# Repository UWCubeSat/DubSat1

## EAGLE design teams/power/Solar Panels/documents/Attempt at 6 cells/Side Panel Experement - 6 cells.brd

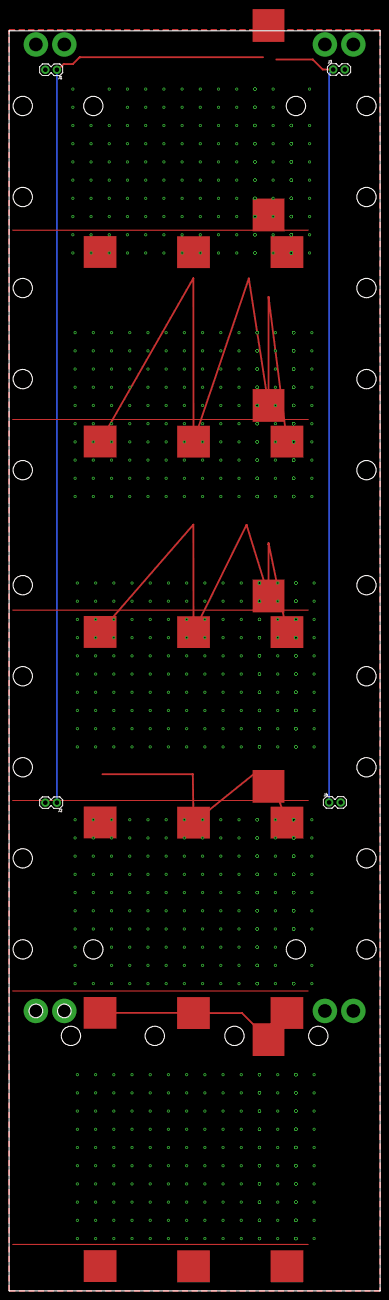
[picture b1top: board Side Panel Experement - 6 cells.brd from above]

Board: 2 copper layers, 81.5 x 276.8 mm, 10 parts (0 on the bottom side), 7 nets.

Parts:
J1, J2, J3, J4: 1X02
SOLAR_1, SOLAR_2, SOLAR_3, SOLAR_4, SOLAR_5, SOLAR_6: SOLAR_CELL_HALF_TABSFULL_TABS; SOLAR_CELL_3G30A_FULL_TABS

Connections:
1-2: SOLAR_1.P$1, SOLAR_2.P$F1, SOLAR_2.P$F2, SOLAR_2.P$F3
2-3: SOLAR_2.P$1, SOLAR_3.P$F1, SOLAR_3.P$F2, SOLAR_3.P$F3
3-4: SOLAR_3.P$1, SOLAR_4.P$F1, SOLAR_4.P$F2, SOLAR_4.P$F3
4-5: SOLAR_4.P$1, SOLAR_5.P$F1, SOLAR_5.P$F2, SOLAR_5.P$F3
GND: J1.2, J2.2, J3.2, J4.2, SOLAR_1.P$F1, SOLAR_1.P$F2, SOLAR_1.P$F3
unnamed: SOLAR_5.P$1, SOLAR_6.P$F1, SOLAR_6.P$F2, SOLAR_6.P$F3
VOUT: J1.1, J2.1, J3.1, J4.1

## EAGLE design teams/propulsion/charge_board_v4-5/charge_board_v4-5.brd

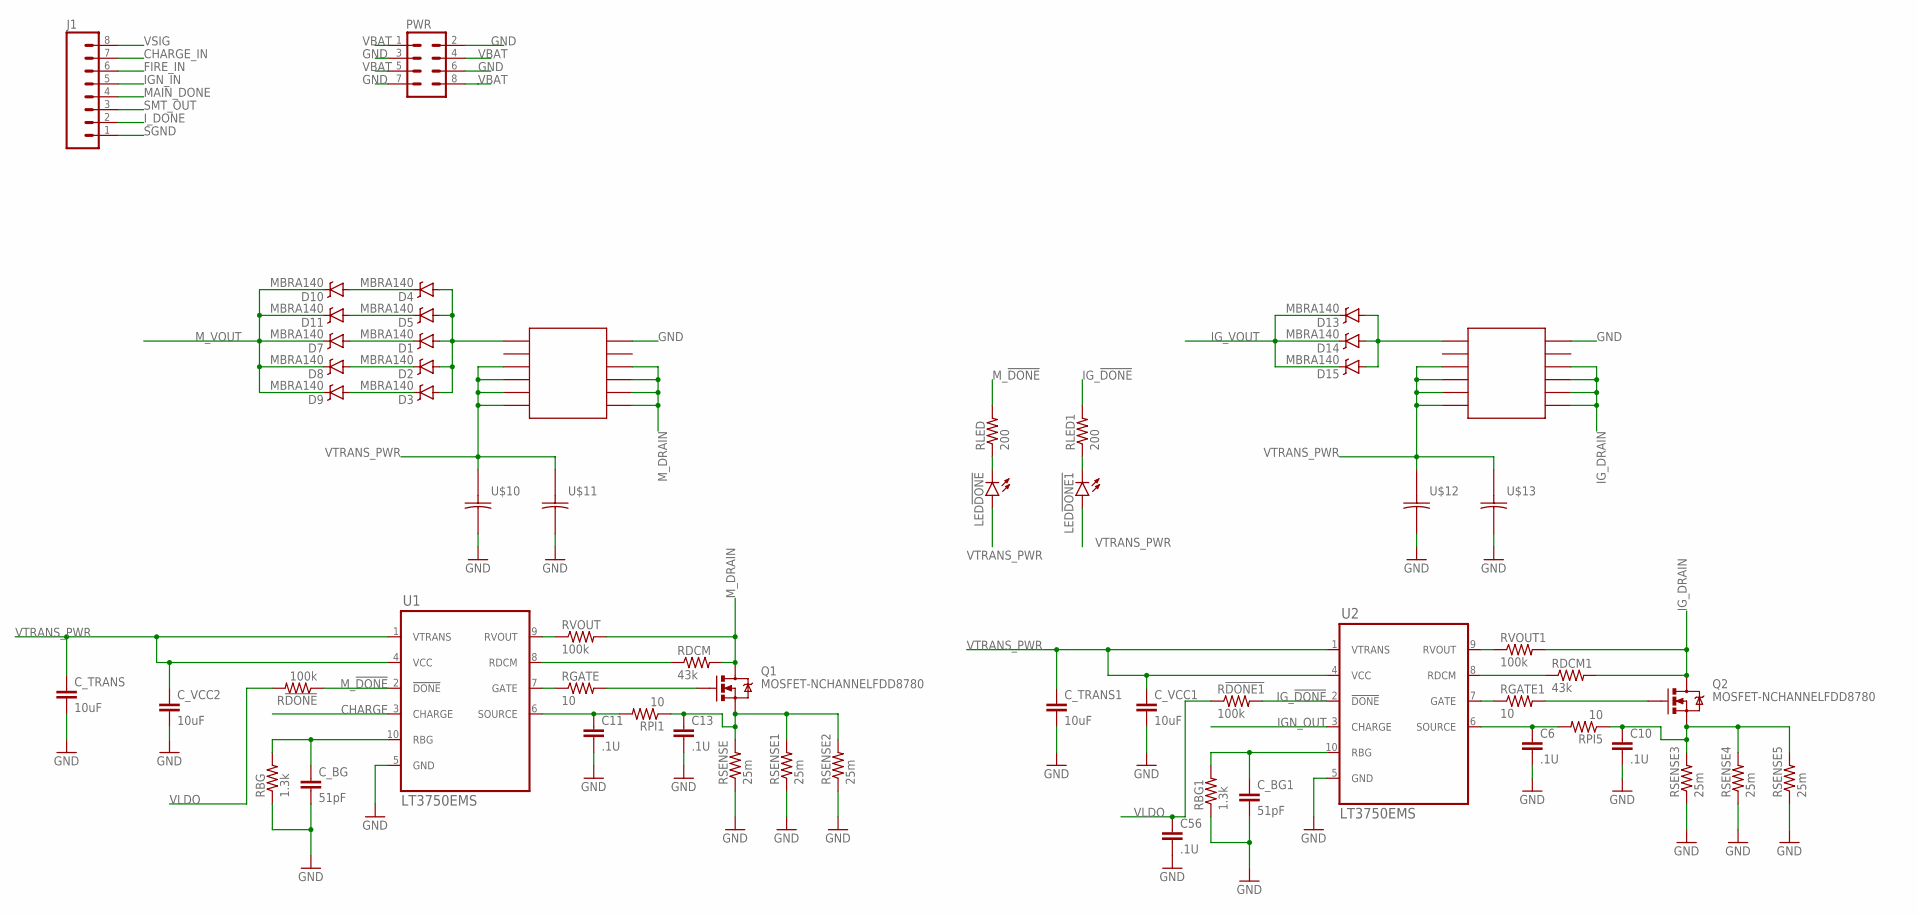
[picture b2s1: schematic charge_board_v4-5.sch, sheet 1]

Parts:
C6, C10, C11, C13, C56: .1U; 0805
C_BG, C_BG1: 51pF; 0805
C_TRANS, C_TRANS1: 10uF; 0805
C_VCC1, C_VCC2: 10uF; 0805
D1, D2, D3, D4, D5, D7, D8, D9, D10, D11, D13, D14, D15: MBRA140; SMA-DIODE
J1: M08; 1X08_ROUND
LED!DONE, LED!DONE1: LED1206; LED-1206
PWR: M04X2; 2X4
Q1, Q2: MOSFET-NCHANNELFDD8780; DPAK
R!DONE, R!DONE1: 100k; 0805
RBG, RBG1: 1.3k; 0805
RDCM, RDCM1: 43k; 0805
RGATE, RGATE1: 10; 0805
RLED, RLED1: 200; 0805
RPI1, RPI5: 10; 0805
RSENSE, RSENSE1, RSENSE2, RSENSE3, RSENSE4, RSENSE5: 25m; 0805
RVOUT, RVOUT1: 100k; 0805
U1, U2: LT3750EMS; MSOP10
U$1: COILCRAFT_DA2034; DA2034
U$2: COILCRAFT_DA2033; DA2033
U$10, U$11, U$12, U$13: PANASONIC_16SVPG270M; PANASONIC_SVPG

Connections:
7: RGATE1.1, U2.7 (GATE)
8: RDCM1.1, U2.8 (RDCM)
9: RVOUT1.1, U2.9 (RVOUT)
CHARGE: U1.3 (CHARGE); also elsewhere on the board
CHARGE_IN: J1.7; also elsewhere on the board
FIRE_IN: J1.6; also elsewhere on the board
GND: C6.2, C10.2, C11.2, C13.2, C56.2, C_BG.2, C_BG1.2, C_TRANS.2, C_TRANS1.2, C_VCC1.2, C_VCC2.2, PWR.2, PWR.3, PWR.6, PWR.7, RBG.1, RBG1.1, RSENSE.1, RSENSE1.1, RSENSE2.1, RSENSE3.1, RSENSE4.1, RSENSE5.1, U1.5 (GND), U2.5 (GND), U$1.P$12, U$2.P$12, U$10.NEG, U$11.NEG, U$12.NEG, U$13.NEG; also elsewhere on the board
IGN_IN: J1.5; also elsewhere on the board
IGN_OUT: U2.3 (CHARGE); also elsewhere on the board
IG_!DONE: R!DONE1.2, RLED1.2, U2.2 (!DONE); also elsewhere on the board
IG_BG: C_BG1.1, RBG1.2, U2.10 (RBG)
IG_DRAIN: Q2.4 (D), RDCM1.2, RVOUT1.2, U$2.P$7, U$2.P$8, U$2.P$9, U$2.P$10
IG_GATE: Q2.1 (G), RGATE1.2
IG_SENSE: C10.1, Q2.3 (S), RPI5.1, RSENSE3.2, RSENSE4.2, RSENSE5.2
IG_VOUT: D13.C, D14.C, D15.C; also elsewhere on the board
I_DONE: J1.2; also elsewhere on the board
MAIN_DONE: J1.4; also elsewhere on the board
M_!DONE: R!DONE.1, RLED.2, U1.2 (!DONE); also elsewhere on the board
M_BG: C_BG.1, RBG.2, U1.10 (RBG)
M_DRAIN: Q1.4 (D), RDCM.2, RVOUT.2, U$1.P$7, U$1.P$8, U$1.P$9, U$1.P$10
M_GATE: Q1.1 (G), RGATE.2
M_SCHMITT: J1.2
M_SENSE: C13.1, Q1.3 (S), RPI1.1, RSENSE.2, RSENSE1.2, RSENSE2.2
M_VOUT: D7.C, D8.C, D9.C, D10.C, D11.C; also elsewhere on the board
unnamed: C6.1, RPI5.2, U2.6 (SOURCE)
unnamed: RVOUT.1, U1.9 (RVOUT)
unnamed: D4.C, D10.A
unnamed: RDCM.1, U1.8 (RDCM)
unnamed: RGATE.1, U1.7 (GATE)
unnamed: D5.C, D11.A
unnamed: D1.C, D7.A
unnamed: D2.C, D8.A
unnamed: D3.C, D9.A
unnamed: LED!DONE.C, RLED.1
unnamed: LED!DONE1.C, RLED1.1
unnamed: D1.A, D2.A, D3.A, D4.A, D5.A, U$1.P$1
unnamed: C11.1, RPI1.2, U1.6 (SOURCE)
unnamed: D13.A, D14.A, D15.A, U$2.P$1
SGND: J1.1; also elsewhere on the board
SMT_OUT: J1.3; also elsewhere on the board
VBAT: PWR.1, PWR.4, PWR.5, PWR.8; also elsewhere on the board
VLDO: C56.1, R!DONE.2, R!DONE1.1; also elsewhere on the board
VSIG: J1.8; also elsewhere on the board
VTRANS_PWR: C_TRANS.1, C_TRANS1.1, C_VCC1.1, C_VCC2.1, LED!DONE.A, LED!DONE1.A, U1.1 (VTRANS), U1.4 (VCC), U2.1 (VTRANS), U2.4 (VCC), U$1.P$3, U$1.P$4, U$1.P$5, U$1.P$6, U$2.P$3, U$2.P$4, U$2.P$5, U$2.P$6, U$10.POS, U$11.POS, U$12.POS, U$13.POS; also elsewhere on the board

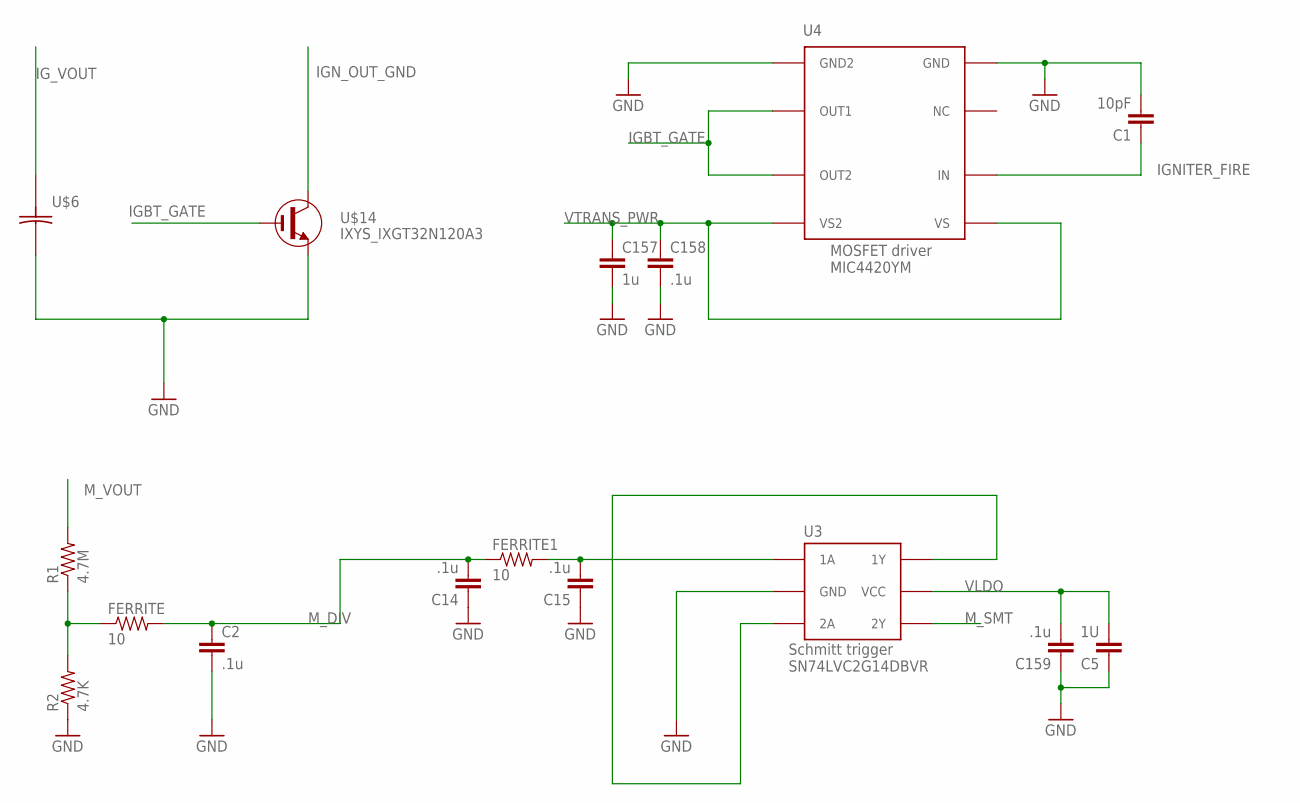
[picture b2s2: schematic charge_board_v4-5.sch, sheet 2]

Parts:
C1: 10pF; 0805
C2, C14, C15, C158, C159: .1u; 0805
C5: 1U; 0805
C157: 1u; 0805
FERRITE, FERRITE1: 10; 0805
R1: 4.7M; R2010
R2: 4.7K; R2010
U3: TI_SCHMITTRIGGER_SN74; SOT-23-6
U4: MICREL_MOSFETDRIVER_MIC4420; 8-SOIC
U$6: KEMET_LDEQH3100KA5N00; KEMET_F3078
U$14: IXYS_IXGT32N120A3; TO-268

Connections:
GND: C1.2, C2.2, C5.1, C14.1, C15.1, C157.2, C158.2, C159.1, R2.1, U3.P$2 (GND), U4.P$4 (GND), U4.P$5 (GND2), U$6.NEG, U$14.3 (E); also elsewhere on the board
IGBT_GATE: U4.P$6 (OUT1), U4.P$7 (OUT2), U$14.1 (G)
IGNITER_FIRE: C1.1, U4.P$2 (IN); also elsewhere on the board
IGN_OUT_GND: U$14.2 (C)
IG_VOUT: U$6.POS; also elsewhere on the board
M_DIV: C2.1, C14.2, FERRITE.2, FERRITE1.1
M_SMT: U3.P$4 (2Y); also elsewhere on the board
M_VOUT: R1.2; also elsewhere on the board
unnamed: U3.P$3 (2A), U3.P$6 (1Y)
unnamed: C15.2, FERRITE1.2, U3.P$1 (1A)
unnamed: FERRITE.1, R1.1, R2.2
VLDO: C5.2, C159.2, U3.P$5 (VCC); also elsewhere on the board
VTRANS_PWR: C157.1, C158.1, U4.P$1 (VS), U4.P$8 (VS2); also elsewhere on the board

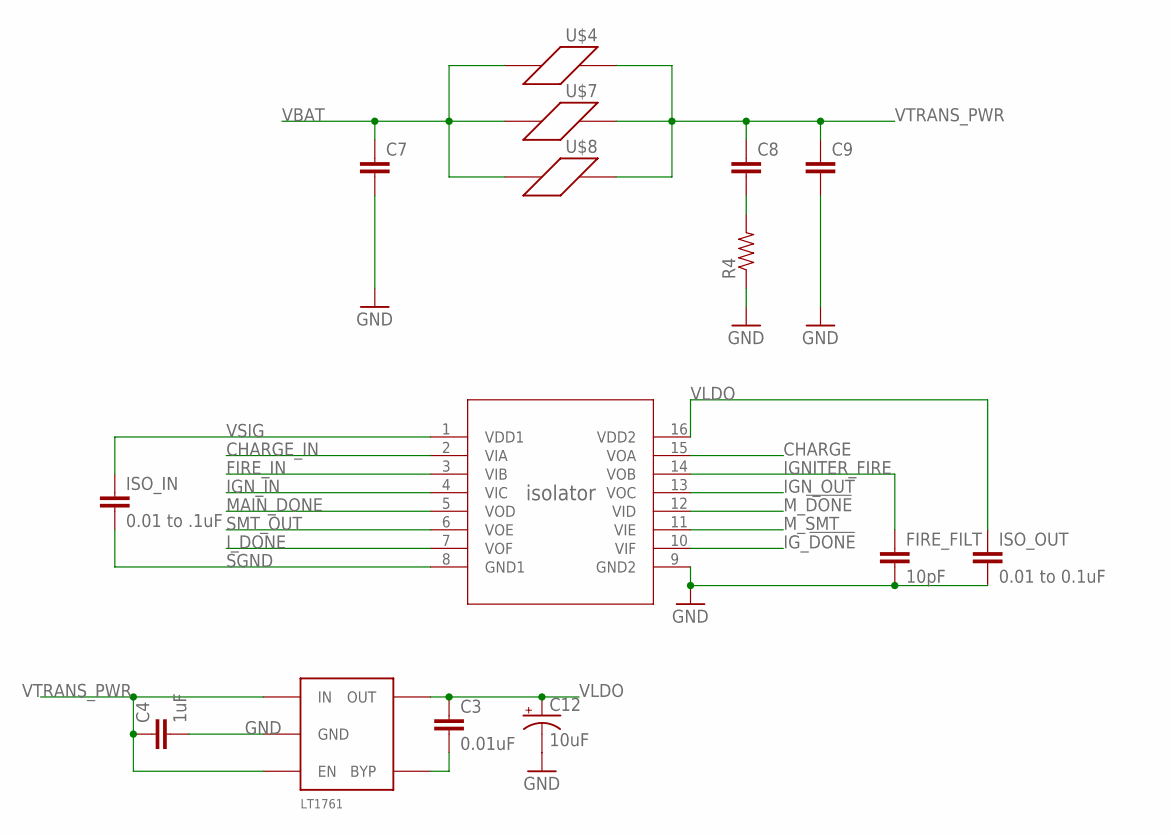
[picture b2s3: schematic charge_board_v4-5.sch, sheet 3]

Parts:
ADUM163N: ADUM163N1BRZ; R_16
C3: 0.01uF; 0805
C4: 1uF; 0805
C7, C8, C9: CAP0805; 0805
C12: 10uF; EIA3216
FIRE_FILT: 10pF; 0805
ISO_IN: 0.01 to .1uF; 0805
ISO_OUT: 0.01 to 0.1uF; 0805
LDO: LINEAR_LDO_LT1761-X; SOT-23-5
R4: RESISTOR0805-RES; 0805
U$4: B.L1_FBMJ2125HS420-T; 0805
U$7: B.L2_FBMH1608HL121-T; 0603
U$8: I.L1_587-3855-1-ND; 1206

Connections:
CHARGE: ADUM163N.15 (VOA); also elsewhere on the board
CHARGE_IN: ADUM163N.2 (VIA); also elsewhere on the board
FIRE_IN: ADUM163N.3 (VIB); also elsewhere on the board
GND: ADUM163N.9 (GND2), C4.2, C7.2, C9.2, C12.C (-), FIRE_FILT.2, ISO_OUT.2, LDO.P$2 (GND), R4.1; also elsewhere on the board
IGNITER_FIRE: ADUM163N.14 (VOB), FIRE_FILT.1; also elsewhere on the board
IGN_IN: ADUM163N.4 (VIC); also elsewhere on the board
IGN_OUT: ADUM163N.13 (VOC); also elsewhere on the board
IG_!DONE: ADUM163N.10 (VIF); also elsewhere on the board
I_DONE: ADUM163N.7 (VOF); also elsewhere on the board
MAIN_DONE: ADUM163N.5 (VOD); also elsewhere on the board
M_!DONE: ADUM163N.12 (VID); also elsewhere on the board
M_SMT: ADUM163N.11 (VIE); also elsewhere on the board
unnamed: C3.2, LDO.P$4 (BYP)
unnamed: C8.2, R4.2
SGND: ADUM163N.8 (GND1), ISO_IN.2; also elsewhere on the board
SMT_OUT: ADUM163N.6 (VOE); also elsewhere on the board
VBAT: C7.1, U$4.1, U$7.1, U$8.1; also elsewhere on the board
VLDO: ADUM163N.16 (VDD2), C3.1, C12.A (+), ISO_OUT.1, LDO.P$5 (OUT); also elsewhere on the board
VSIG: ADUM163N.1 (VDD1), ISO_IN.1; also elsewhere on the board
VTRANS_PWR: C4.1, C8.1, C9.1, LDO.P$1 (IN), LDO.P$3 (EN), U$4.2, U$7.2, U$8.2; also elsewhere on the board

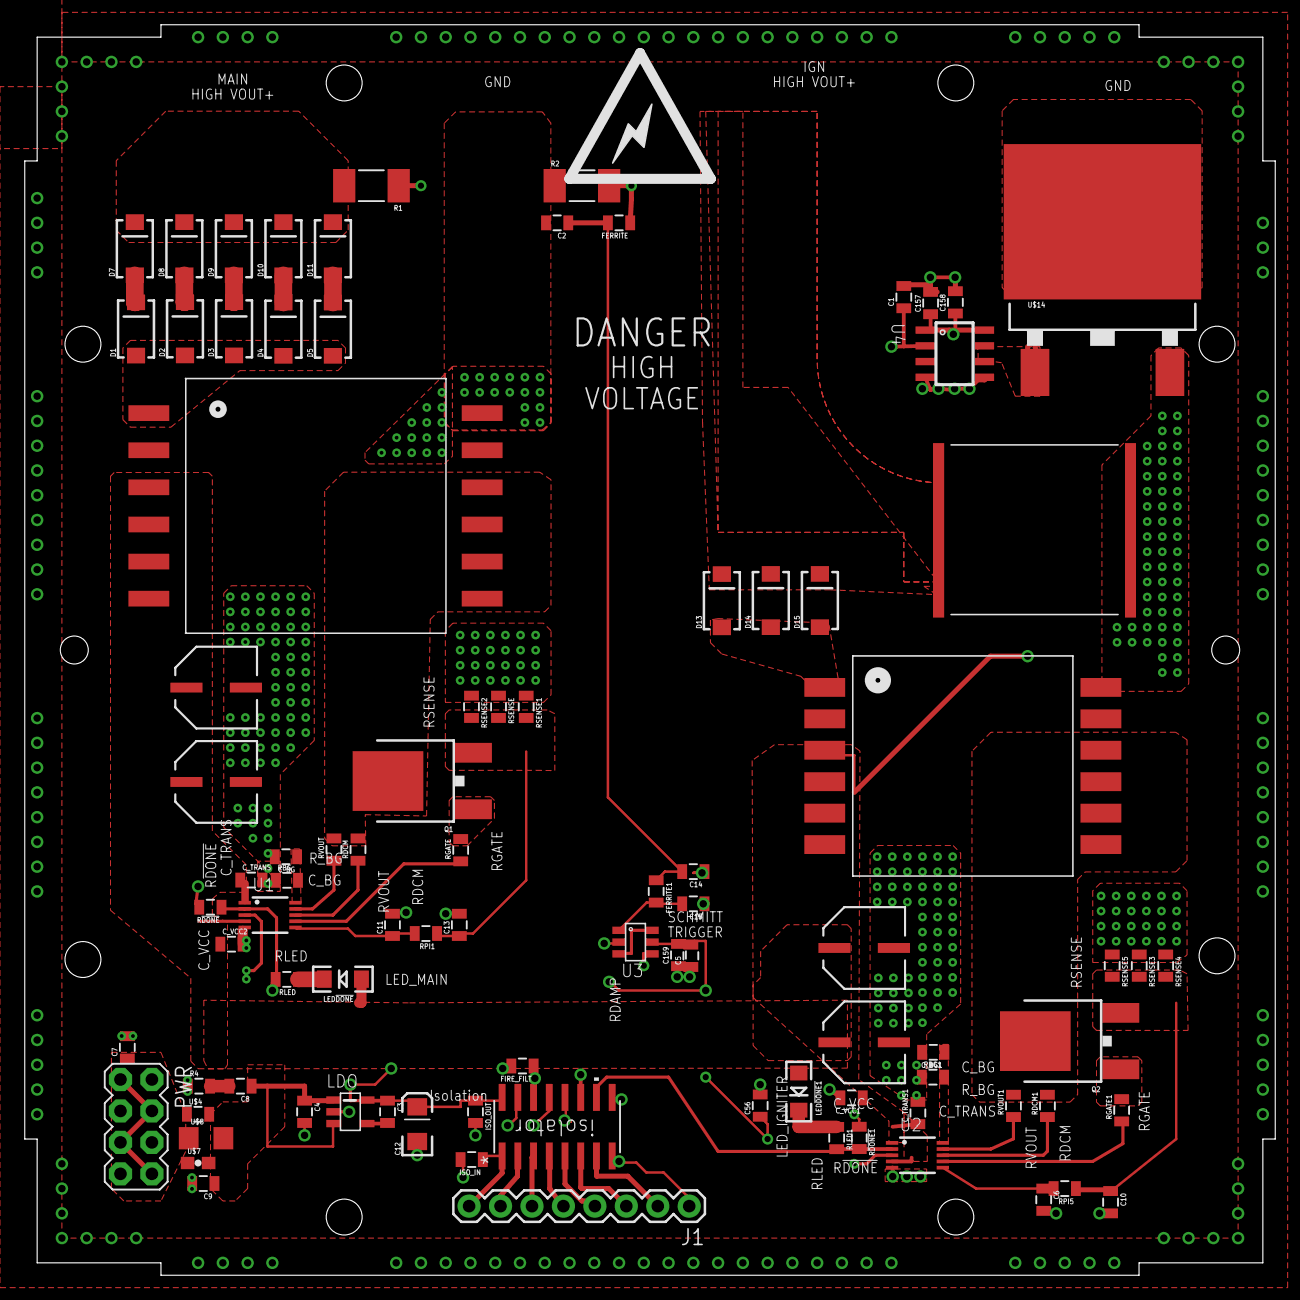
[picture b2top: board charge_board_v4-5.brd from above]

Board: 4 copper layers, 101.0 x 101.0 mm, 90 parts (0 on the bottom side), 52 nets.

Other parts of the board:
U$3: ICON_BOLT-L

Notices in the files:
parts and their libraries:
SparkFun-Connectors: Licensing: Creative Commons ShareAlike 4.0 International - https://creativecommons.org/licenses/by-sa/4.0
dicons: Copyright (C) 2004, Bob Starr (rtzaudio@mindspring.com)
